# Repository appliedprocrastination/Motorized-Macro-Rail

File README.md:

# OpenMacroRail Electronics Hardware
## Summary
PCB-design for controlling a motorized macro rail. Designed for photographers with electronics skills rather than engineers with photography skills. Main features:
- Zero surface mount components, and should therefore be possible to hand solder - even for people with novice soldering skills. 
- Flexible solution for connecting to most types of camera via 2.5mm stereo jack, pin header, or solder joints.
- Simple design for driving a single motor via a BTT TMC2209 V1.2 motor driver.
- Based on the WiFi-enabled NodeMCU 32S V2 DevKit. 
- Has broken out headers for connecting limit switches and rotary encoders (neither of which are used in the intended application the board was designed for).
- Total cost of around $30 (Camera, optics, motor, slider, and tools not included)

### Other parts of this project:
- [Firmware and web-interface](https://github.com/AppliedProcrastination/OpenMacroRail)
- [3D printable gears and PCB mount](https://www.printables.com/model/219042-motorized-camera-rail-for-macro-photography) 
- [3D printable microscope objective adapter](https://www.printables.com/model/218910-microscope-objective-adapter) (RMS Thread 160mm focal distance)
- [Canon EF/EF-S mount for the microscope adapter above](https://www.printables.com/model/218900-canon-efef-s-lens-mount-with-screw-holes)
- Section of README with links to other relevant documentation: [Various Documentation](#various-documentation)

## Configurability
The design is quite adaptable in general, and there are few components that are completely necessary for functioning (see the section "Minimum viable design"). There is however one part of the circuit that is particularly adaptable, and requires the users attention to guarantee a working configuration: the shutter control circuit - which depends on what kind of camera you are planning to control with this setup.

Snippet of schematic (DNP = Do Not Place):

As shown in the image above, there is a lot going on for what is normally a very simple circuit (you can trigger many cameras by simply short-circuiting all the pins in the remote shutter connector with a piece of wire). The reason for all this additional complexity is to keep the design as flexible as possible, and hopefully allow the PCB to be used with any type of camera. This is obviously not possible for me to test out in person, so I'm basing most of what follows on [this blog-post by Günter from LRTimelapse](https://lrtimelapse.com/news/intervalometer-hack/) (which is based on feedback from a solid photographer community) and private conversations with Stefan from [CNCKitchen](https://www.youtube.com/CNCKitchen) (as he owns a camera not mentioned in the above blog-post).

All the extra nick-nack is an attempt to solve the following design-requirements:
1. Different cameras require different signals to trigger
    - Example: 
        - Canon requires Shutter and GND to be shorted
        - Nikon/Sony requires Shutter, Focus and GND to be shorted
        - Lumix requires a [resistor network](https://i1.wp.com/fluxing.de/wp-content/uploads/2018/03/arduino-panasonic-lumix-shutter-schematic.jpg) between Shutter and GND.
2. Different cameras may swap the layout of Shutter and Focus signals on the 2.5mm jack
3. The user may not own a connector with a 2.5mm jack, so a pin header/2.54mm pitch solder joint option is also provided.
4. The high currents drawn by the motor may cause noise on the PCB, so therefore the shutter circuit is optically isolated from the rest of the electronics to avoid unintended triggering of the camera shutter.

The following components are layed out in the design solely to handle requirements 1. and 2.
- SJ1, SJ2, SJ3
- R2, R3 (Note: These are, to my knowledge, only required by Lumix - and should not be mounted by default)

The solder jumpers (SJ1-3) are there to give the user an opportunity to make permanent (but recoverable) changes to the circuit. The way this works is that each SJ consists of two exposed copper pads with a small trace connecting the pads. Cutting the trace with a scalpel will remove the connection between the pads, but it is still possible to recover this connection by applying a bit of solder as a bridge between the pads (in case the user buys a new camera, or just cut the wrong wire).

### An example of how to use solder jumpers:
Suppose your camera starts updating the screen each time the autofocus-signal is activated (even in manual focus mode), so you want to stop that signal from being activated each time a picture is captured. In this scenario, you can use a scalpel to break the wire connecting the two pads of SJ2 by cutting along the red arrow in the following picture: 

### Default configuration (Canon,Nikon,Sony):
The default configuration requires you to not mount R2 and R3. The pads on all the solder jumpers are shorted by default, meaning that a simplified schematic of the circuit looks like this:

This should work for most Canon, Nikon, and Sony cameras.

### Lumix configuration:
To use the shutter circuit with a Lumix camera, the resistor network must be mounted (R2 and R3). Keep in mind that SJ1 is shorted by default, meaning that it needs to be cut in order for R2 to take any effect.

Mount R2 and R3, then use a scalpel to break the wire in SJ1 by cutting along the red arrow in this picture.

Cutting this wire will activate R2 and leave you with the following schematic:

## Layout Options 
In the folder named Outputs/Gerber you will find design files that can be sent to a PCB manufacturer for production. There are two options, A and B, which differ only in the orientation of the power connector. 

The reason that there are two options is to accommodate for mounting the PCB on different tripod designs. Keep in mind that the PCB is mounted on a moving part of the macro rail, so protruding parts may get stuck or bent by the force from the motor.

## Bill Of Materials (BOM)
*Most of the AliExpress links are affiliate links. Prices are estimates and may vary with your location (shipping cost)*

### On PCB:
 - [PCB itself](./Outputs/Gerber/MacroRail_V1_0-2022-02-26.zip). Ca $10 at JLCPCB
 - 1x [TMC2209-V1.2](https://s.click.aliexpress.com/e/_9uc1XB) Stepper motor driver ([Documentation](https://github.com/bigtreetech/BIGTREETECH-TMC2209-V1.2/)). ca $8
 - 1x [NodeMCU 32s V2](https://www.aliexpress.com/item/1005001636295529.html) Dev kit (38-pin version) ([Documentation](https://docs.ai-thinker.com/en/esp32/boards/nodemcu_32s)) ca $5
 - 1x [PC817 Optocoupler](https://s.click.aliexpress.com/e/_AAgoAp) ca $1
 - 1x [100 uF capacitor (35V)](https://s.click.aliexpress.com/e/_ADnqKh) ca $1
 - 1x [10 uF capacitor (25V)](https://s.click.aliexpress.com/e/_ADnqKh) ca $1
 - 1x [1 uF capacitor](https://s.click.aliexpress.com/e/_9j2jOz) ca $1
 - 1x [2.1 mm Barrel Jack (power)](https://s.click.aliexpress.com/e/_Aq01NT) ca $1
 - 1x [Selection of resistors](https://s.click.aliexpress.com/e/_AOqGqt) (depending on your camera) ca $1
    - Note: R1 and R4 must always be mounted (these are 600 Ohm and 1k Ohm resistors respectively)
 - 1x [SJ1-2503A 2.5 mm stereo jack receptacle (for shutter cable)](https://no.mouser.com/ProductDetail/CUI-Devices/SJ1-2503A?qs=WyjlAZoYn52728cbIH3aBA%3D%3D) ca $1 (optional)
 - 1x [4-pin screw terminal block](https://s.click.aliexpress.com/e/_97dipR) ca $2 (optional)
 - 1x [TIP120 transistor (for powering external LED lighting)](https://s.click.aliexpress.com/e/_ApnAYv) ca $1 (optional) 
 - 3x [3-pin pin row](https://s.click.aliexpress.com/e/_ABvcat) ca $1 (optional)
 - 1x [4-pin pin row](https://s.click.aliexpress.com/e/_ABvcat) ca $1 (optional)
 - 1x [2-pin pin row](https://s.click.aliexpress.com/e/_ABvcat) ca $1 (optional)
 - 2x [19-pin pin header](https://s.click.aliexpress.com/e/_AFHrY5) ca $2 (optional)
 - 2x [8-pin pin header](https://s.click.aliexpress.com/e/_AFHrY5) ca $1 (optional)
 - 1x [2-pin pin header](https://s.click.aliexpress.com/e/_AFHrY5) ca $1 (optional)

 Total on PCB: ca $40 ($29 when excluding optional components)

### Outside of PCB:
Mandatory parts:
 - [Macro Rail](https://s.click.aliexpress.com/e/_9IiOvB) ca. $20 
 - [Nema 14 high torque motor](https://s.click.aliexpress.com/e/_ArX3ot) (High torque may be unnecessary for moving compact cameras) ca $20
 - RMS threaded microscope lens (focused to 160mm). [Example](https://s.click.aliexpress.com/e/_9zATGv) ca $8
 - 5-12V Power supply (current can be limited with TMC2209 if 5V is too much for your motor). [Example](https://s.click.aliexpress.com/e/_AC81D7) ca $8 
 - Cable for shutter release that fits your camera (you can either use the 2.5mm jack receptacle or cut the cable and solder it directly to the PCB via JP1)
    - [Example for various cameras](https://s.click.aliexpress.com/e/_9iNl7J) ca $3

Parts that can be 3D-printed if you design something that suits your camera:
 - Bellow spacer that fits your camera (with converters to hold the microscope lens). This is optional, and can be 3D printed instead. 
    - Examples for Canon 5D:
        - [Bellow spacer](https://s.click.aliexpress.com/e/_A5xnYt) ca $40
        - [EFS to M24 converter](https://s.click.aliexpress.com/e/_9QvErF) ca $5
        - [M42 to RMS converter](https://s.click.aliexpress.com/e/_9QPTOd) ca $5
 
Total outside of PCB: ca $109 ($59 when excluding parts that can be 3D-printed)

## Preview

### Top

### Bottom

### Minimum viable design
Note: You may need to mount more resistors to get a minimum viable design (depending on your camera)

## How to order a printed circuit board (PCB)?
If you are interested in this project, and feel comfortable soldering electronic components, but have never ordered a custom PCB before this section is for you. 

Hobby-grade PCB manufacturers have made the process of ordering custom PCBs incredibly simple (and cheap) over the last few years, so for a low complexity board like this one, ordering can be done without any prior knowledge of the manufacturing process. 

### Step by step guide:

1. Decide whether you want your power connector oriented sideways (Option A) or downwards (Option B). Try to think about whether the power cable may get in the way of movement the tripod you plan to mount your macro rail to. See the section about [Layout Options](#layout-options) for more info.
2. Download the .zip file corresponding to your preferred layout option from the folder [/Outputs/Gerber](/Outputs/Gerber/). This is the design file that you will send to the manufacturer for fabrication.
3. Go to your preferred PCB manufacturers website and upload the gerber file. This board was designed for using https://www.jlcpcb.com, which is a very cheap, and fast, hobby-grade manufacturer. 

4. Once the upload is complete, you will see a preview of the board, and the web-tool will have learned most of the important parameters of the design (like the size, how many layers of copper it contains, etc.)

5. There's only one important thing you may need to fill in, which is the order of the layers. For some reason, the web-tool doesn't recognize the _l1, _l2, _l3, and _l4, suffixes of each layer, so you need to select these layers as shown in the image below. 

While you are at it, make sure to select the sexy black soldermask, and click "specify a location" for the order number. The last setting will ensure that the manufacturer doesn't place an order number anywhere important, but rather replace a predefined string like shown here:

6. That's it! Click "Save to cart", pay, and the board will be manufactured and shipped towards you within a two or three days (typically). Note that there is a cheap shipping option kind of hidden in the menu. If you didn't already have all the other necessary components in your electronics stockpile, it might be a good idea to consider this "slow" shipping option since you are already waiting for other stuff. In my experience, the PCBs arrive between 2 and 3 weeks after placing your order (when using the cheapest shipping option).

## Various documentation:
- [NodeMCU-32S Core Development Board](https://docs.ai-thinker.com/en/esp32/boards/nodemcu_32s)
- [NodeMCU Arduino Core (Software)](https://github.com/espressif/arduino-esp32)
- [TMC2209-V1.2 manual (Motor driver module)](https://github.com/bigtreetech/BIGTREETECH-TMC2209-V1.2/blob/master/manual/TMC2209-V1.2-manual.pdf)
- [TMC2209 datasheet (chip itself)](https://www.trinamic.com/fileadmin/assets/Products/ICs_Documents/TMC2209_datasheet_rev1.07.pdf)

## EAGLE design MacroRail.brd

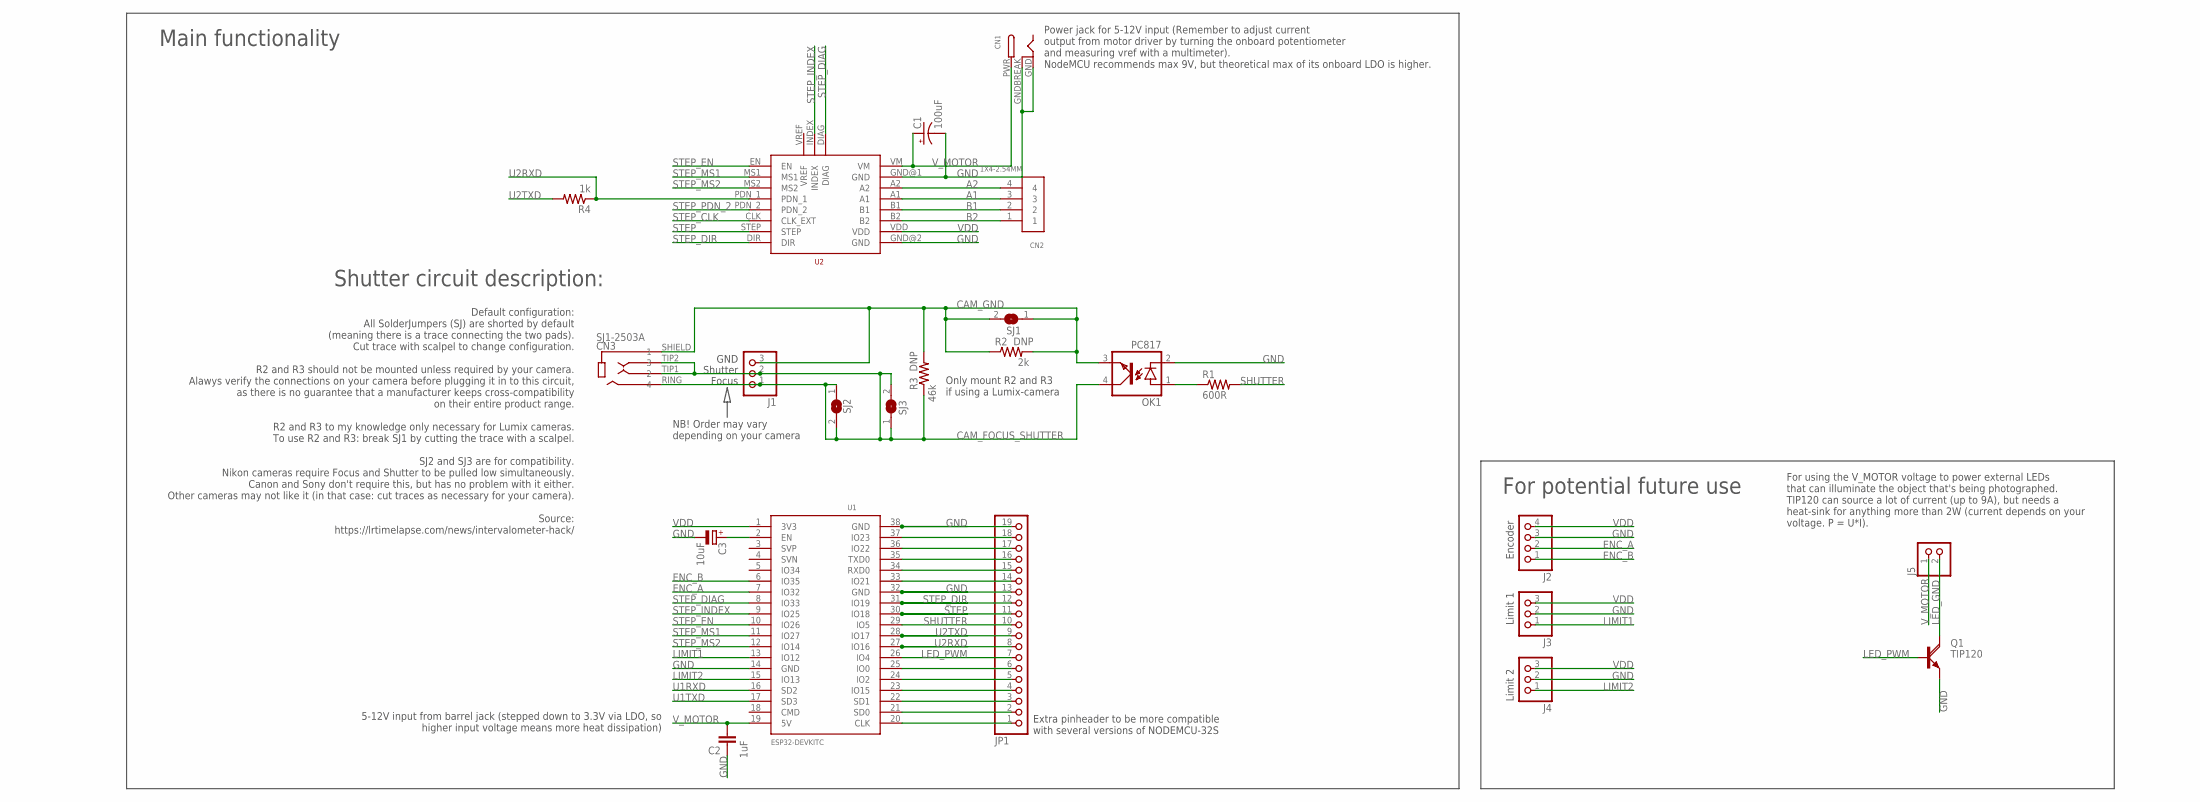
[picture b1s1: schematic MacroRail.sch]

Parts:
C1: 100uF; E5-8,5
C2: 1uF; C050-024X044
C3: 10uF; E1,8-4
CN1: DCBARRELPTH; DCJACK_2MM_PTH
CN2: 1X4-2.54MM; 1X04-2.54MM
CN3: SJ1-2503A; STEREOJACK2.5MM_STEREOJACK2.5MM
J1, J3, J4: PINHD-1X3CB; 1X03-CLEANBIG
J2: PINHD-1X4; 1X04
J5: PINHD-1X2CLEAN; 1X02CLEAN
JP1: PINHD-1X19; 1X19
OK1: PC817; DIL04
Q1: TIP120; TO220AH
R1: 600R; 0207/7
R2: 2k; 0207/7
R3: 46k; 0207/7
R4: 1k; 0207/7
SJ1, SJ2, SJ3: SJ
U1: ESP32DEVKITCWIDE; NODEMCU-32S
U2: TMC2209-V1.2+INDEX; BIGTREETECH-TMC2209-V1.2+INDEX

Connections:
A1: CN2.3, U2.A1
A2: CN2.4, U2.A2
B1: CN2.2, U2.B1
B2: CN2.1, U2.B2
CAM_FOCUS_SHUTTER: CN3.RING (4), CN3.TIP1 (2), CN3.TIP2 (3), J1.1, J1.2, OK1.4 (COL), R3.1, SJ2.1, SJ2.2, SJ3.1, SJ3.2
CAM_GND: CN3.SHIELD (1), J1.3, OK1.3 (EMIT), R2.1, R2.2, R3.2, SJ1.1, SJ1.2
ENC_A: J2.2, U1.7 (IO32)
ENC_B: J2.1, U1.6 (IO35)
GND: C1.-, C2.1, C3.-, CN1.GND, CN1.GNDBREAK, J2.3, J3.2, J4.2, JP1.13, JP1.19, OK1.2 (C), Q1.E, U1.14 (GND), U1.32 (GND), U1.38 (GND), U2.GND@1 (GND), U2.GND@2 (GND)
LED_GND: J5.2, Q1.C
LED_PWM: JP1.7, Q1.B, U1.26 (IO4)
LIMIT1: J3.1, U1.13 (IO12)
LIMIT2: J4.1, U1.15 (IO13)
unnamed: OK1.1 (A), R1.1
unnamed: C3.+, U1.2 (EN)
unnamed: JP1.18, U1.37 (IO23)
unnamed: JP1.17, U1.36 (IO22)
unnamed: JP1.16, U1.35 (TXD0)
unnamed: JP1.15, U1.34 (RXD0)
unnamed: JP1.14, U1.33 (IO21)
unnamed: JP1.6, U1.25 (IO0)
unnamed: JP1.5, U1.24 (IO2)
unnamed: JP1.4, U1.23 (IO15)
unnamed: JP1.3, U1.22 (SD1)
unnamed: JP1.2, U1.21 (SD0)
unnamed: JP1.1, U1.20 (CLK)
SHUTTER: JP1.10, R1.2, U1.29 (IO5)
STEP: JP1.11, U1.30 (IO18), U2.STEP
STEP_CLK: U2.CLK (CLK_EXT)
STEP_DIAG: U1.8 (IO33), U2.DIAG
STEP_DIR: JP1.12, U1.31 (IO19), U2.DIR
STEP_EN: U1.10 (IO26), U2.EN
STEP_INDEX: U1.9 (IO25), U2.INDEX
STEP_MS1: U1.11 (IO27), U2.MS1
STEP_MS2: U1.12 (IO14), U2.MS2
STEP_PDN_2: U2.PDN_2
U1RXD: U1.16 (SD2)
U1TXD: U1.17 (SD3)
U2RXD: JP1.8, R4.1, U1.27 (IO16), U2.PDN_1
U2TXD: JP1.9, R4.2, U1.28 (IO17)
VDD: J2.4, J3.3, J4.3, U1.1 (3V3), U2.VDD
V_MOTOR: C1.+, C2.2, CN1.PWR, J5.1, U1.19 (5V), U2.VM

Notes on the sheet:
GND
Focus
Shutter
Power jack for 5-12V input (Remember to adjust current output from motor driver by turning the onboard potentiometer and measuring vref with a multimeter). NodeMCU recommends max 9V, but theoretical max of its onboard LDO is higher.
5-12V input from barrel jack (stepped down to 3.3V via LDO, so higher input voltage means more heat dissipation)
Limit 1
Limit 2
Encoder
For potential future use
Main functionality
Default configuration: All SolderJumpers (SJ) are shorted by default (meaning there is a trace connecting the two pads). Cut trace with scalpel to change configuration. R2 and R3 should not be mounted unless required by your camera. Alawys verify the connections on your camera before plugging it in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
Shutter circuit description:
NB! Order may vary depending on your camera
Only mount R2 and R3 if using a Lumix-camera
For using the V_MOTOR voltage to power external LEDs that can illuminate the object that's being photographed. TIP120 can source a lot of current (up to 9A), but needs a heat-sink for anything more than 2W (current depends on your voltage. P = U*I).
Extra pinheader to be more compatible with several versions of NODEMCU-32S

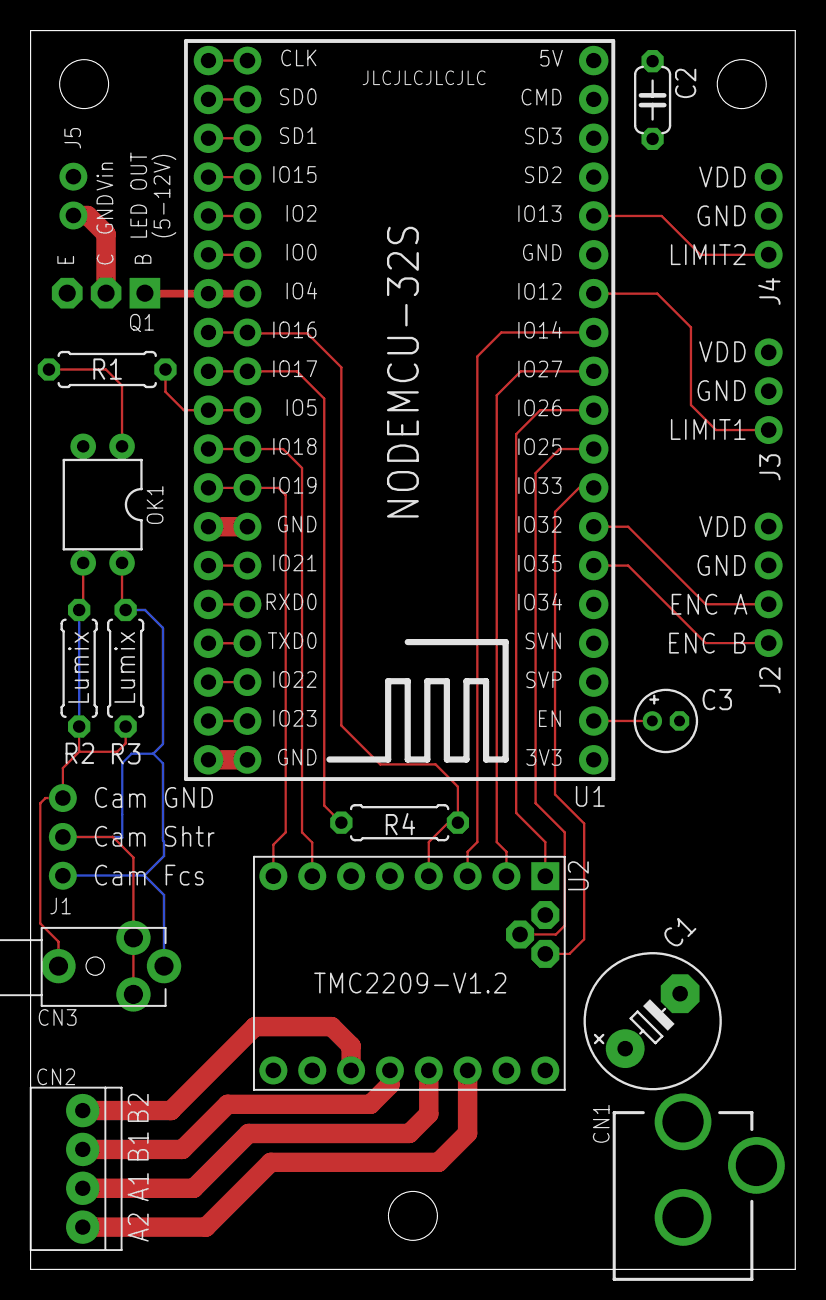
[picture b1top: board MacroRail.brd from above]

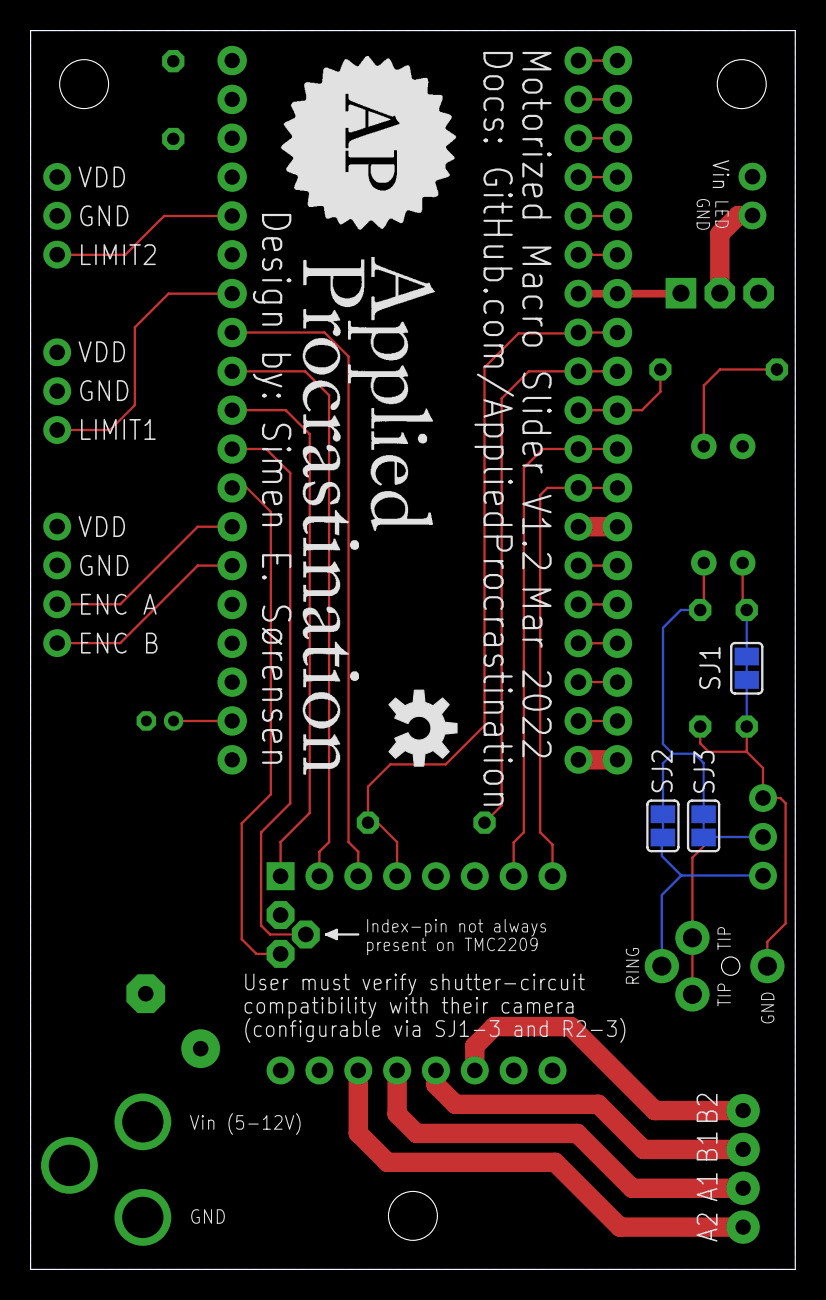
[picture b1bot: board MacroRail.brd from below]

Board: 2 copper layers, 50.0 x 81.0 mm, 25 parts (5 on the bottom side), 38 nets.

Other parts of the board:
U$2: APPLIED-PROCRASTINATION-FULL
U$3: OSHW-LOGO-M

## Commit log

2022-02-23 Update README.md
    Adding pictures in readme
2022-02-24 Add mounting holes and better outputs
2022-02-24 Adding basic BOM to README
    Adding Bill of Materials and links to example Aliexpress listings.
2022-02-25 Redesigned shutter circuit
    Complete redesign of the shutter circuit to make it more flexible and camera agnostic. The user will have to modify the board to match with what their camera expects.
2022-02-26 V1.0
    Redesigned power planes and added more documentation in silk screen.
2022-02-27 Documentation update
    Initial attempt to describe the camera shutter circuitry.
2022-03-05 Modify BOM and clarify README
2022-03-05 Update README.md
    Add header for documentation and collect some of the most useful links there.
2022-03-05 Start V1.1 design
    Add UART Communication between TCM and ESP via SD2 and SD3 pins. Connect DIAG pin. Still undecided whether INDEX pin is necessary as this pin is not always easily accessible on TCM boards.
2022-03-05 Connect DIAG
2022-03-05 V1.1
    Add optional index pin and produce new output files
2022-03-16 Add possibility for driving high power LEDs
    Since good illumination is important for macro photography, an option to drive high power LEDs via the Motorized Macro Rail PCB has been added.
2022-03-22 V1 Revision 1
    Large redesign of the board. Made board wider (50x80mm now). Moved connections to make them more accessible when PCB is mounted on macro slider. Added transistor for driving LED illumination. Added m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
2022-03-22 Remove outdated gerbers
2022-03-26 Move TMC UART communication to Serial2
    Serial1 is already occupied by the ESP flash, so we need to use Serial2 instead. This interface was already in use by the SHUTTER- and LED_PWM-signals, so they had to be moved as well.
2022-04-03 Update documentation to match V1.2
    V1.2 is the first fully functional design
2022-04-03 Add photos and update README
    Add photographs of V1.1 (with bodge wires making it V1.2 in practice) and update readme
2022-04-23 Add section in readme on how to order the PCB
    Add section in readme on how to order the PCB.
    Add more photos
2022-06-04 Update README.md
    Add links to 3D files at Printables.com and to the FW/Web interface project
2022-06-19 Update README.md
    Add OpenMacroRail name to title and clarify which NodeMCU is the correct one.

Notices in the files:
parts and their libraries:
SparkFun-Aesthetics: Licensing: Creative Commons ShareAlike 4.0 International - https://creativecommons.org/licenses/by-sa/4.0
